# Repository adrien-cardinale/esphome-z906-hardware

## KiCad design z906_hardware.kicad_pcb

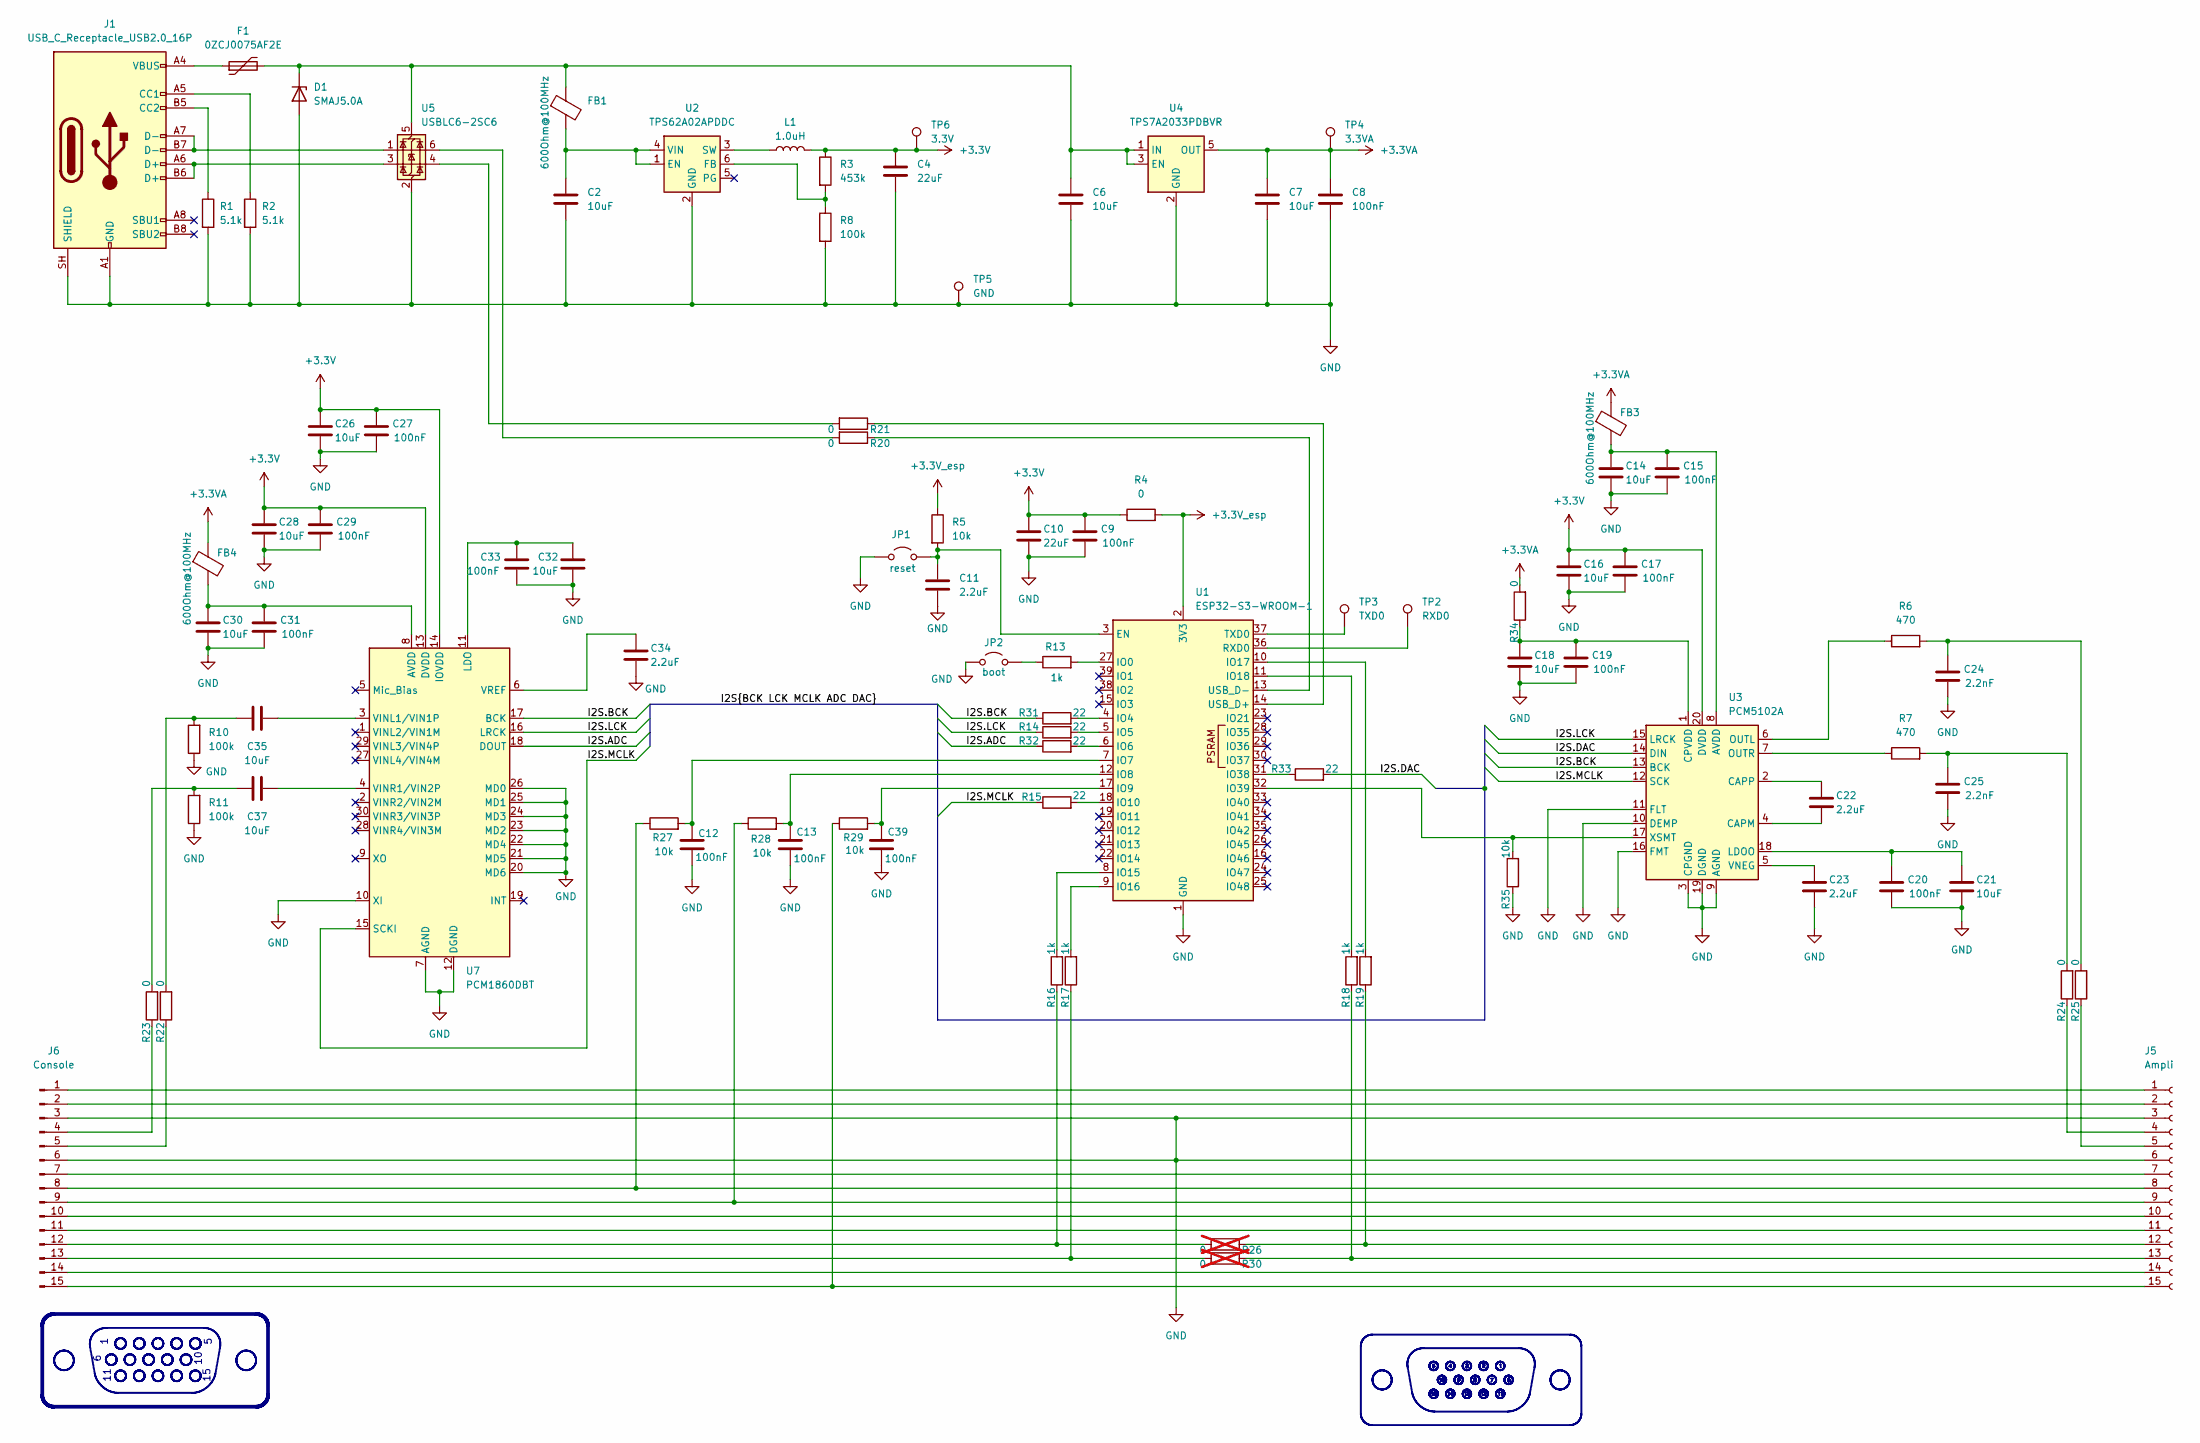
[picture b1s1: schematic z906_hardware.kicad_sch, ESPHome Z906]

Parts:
C2, C6, C7, C14, C16, C18, C21, C26, C28, C30, C32: 10uF; C_0805_2012Metric_Pad1.18x1.45mm_HandSolder
C4, C10: 22uF; C_0805_2012Metric_Pad1.18x1.45mm_HandSolder
C8, C9, C12, C13, C15, C17, C19, C20, C27, C29, C31, C33, C39: 100nF; C_0805_2012Metric_Pad1.18x1.45mm_HandSolder
C11, C22, C23, C34: 2.2uF; C_0805_2012Metric_Pad1.18x1.45mm_HandSolder
C24, C25: 2.2nF; C_0805_2012Metric_Pad1.18x1.45mm_HandSolder
C35, C37: 10uF; C_1206_3216Metric_Pad1.33x1.80mm_HandSolder
D1: SMAJ5.0A; D_SMA
F1: 0ZCJ0075AF2E; Fuse_1210_3225Metric
FB1, FB3, FB4: 600Ohm@100MHz; R_0805_2012Metric_Pad1.20x1.40mm_HandSolder
J1: USB_C_Receptacle_USB2.0_16P; USB_C_Receptacle_GCT_USB4105-xx-A_16P_TopMnt_Horizontal
J5: Ampli; TE_Micro-MaTch_1-215079-6_2x08_P1.27mm_Vertical
J6: Console; DSUB-15-HD_Pins_Horizontal_P2.29x1.90mm_EdgePinOffset3.03mm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
JP1: reset; TestPoint_2Pads_Pitch2.54mm_Drill0.8mm
JP2: boot; TestPoint_2Pads_Pitch2.54mm_Drill0.8mm
L1: 1.0uH; L_1008_2520Metric_Pad1.43x2.20mm_HandSolder
R1, R2: 5.1k; R_0805_2012Metric_Pad1.20x1.40mm_HandSolder
R3: 453k; R_0805_2012Metric_Pad1.20x1.40mm_HandSolder
R4, R20, R21, R22, R23, R24, R25, R34: 0; R_0805_2012Metric_Pad1.20x1.40mm_HandSolder
R5, R27, R28, R29, R35: 10k; R_0805_2012Metric_Pad1.20x1.40mm_HandSolder
R6, R7: 470; R_0805_2012Metric_Pad1.20x1.40mm_HandSolder
R8, R10, R11: 100k; R_0805_2012Metric_Pad1.20x1.40mm_HandSolder
R13, R16, R17, R18, R19: 1k; R_0805_2012Metric_Pad1.20x1.40mm_HandSolder
R14, R15, R31, R32, R33: 22; R_0805_2012Metric_Pad1.20x1.40mm_HandSolder
R26, R30: 0; R_0805_2012Metric_Pad1.20x1.40mm_HandSolder; not fitted
TP2: RXD0; Pin_D1.0mm_L10.0mm
TP3: TXD0; Pin_D1.0mm_L10.0mm
TP4: 3.3VA; Pin_D1.0mm_L10.0mm
TP5: GND; Pin_D1.0mm_L10.0mm
TP6: 3.3V; Pin_D1.0mm_L10.0mm
U1: ESP32-S3-WROOM-1
U2: TPS62A02APDDC; SOT-23-6
U3: PCM5102A; TSSOP-20_4.4x6.5mm_P0.65mm
U4: TPS7A2033PDBVR; SOT-23-5
U5: USBLC6-2SC6; SOT-23-6
U7: PCM1860DBT; TSSOP-30_4.4x7.8mm_P0.5mm

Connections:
+3.3V: C4.1, C9.1, C10.1, C16.1, C17.1, C26.1, C27.1, C28.1, C29.1, L1.2, R3.1, R4.1, TP6.1 (1_1), U3.20 (DVDD), U7.13 (DVDD), U7.14 (IOVDD)
+3.3VA: C7.1, C8.1, FB3.1, FB4.1, R34.2, TP4.1 (1_1), U4.5 (OUT)
+3.3V_esp: R4.2, R5.1, U1.2 (3V3)
/I2S.ADC: R32.1, U7.18 (DOUT)
/I2S.BCK: R31.1, U3.13 (BCK), U7.17 (BCK)
/I2S.DAC: R33.2, U3.14 (DIN)
/I2S.LCK: R14.1, U3.15 (LRCK), U7.16 (LRCK)
/I2S.MCLK: R15.1, U3.12 (SCK), U7.15 (SCKI)
GND: C2.2, C4.2, C6.2, C7.2, C8.2, C9.2, C10.2, C11.2, C12.2, C13.2, C14.2, C15.2, C16.2, C17.2, C18.2, C19.2, C20.2, C21.2, C23.2, C24.2, C25.2, C26.2, C27.2, C28.2, C29.2, C30.2, C31.2, C32.2, C33.2, C34.2, C39.2, D1.2 (A), J1.A1 (GND), J1.A12 (GND), J1.B1 (GND), J1.B12 (GND), J1.SH (SHIELD), J5.3, J5.6, J6.3, J6.6, JP1.1 (A), JP2.1 (A), R1.2, R2.2, R8.2, R10.1, R11.1, R35.1, TP5.1 (1_1), U1.1 (GND), U1.40 (GND), U1.41 (GND), U2.2 (GND), U3.3 (CPGND), U3.9 (AGND), U3.10 (DEMP), U3.11 (FLT), U3.16 (FMT), U3.19 (DGND), U4.2 (GND), U5.2 (GND), U7.7 (AGND), U7.10 (XI), U7.12 (DGND), U7.20 (MD6), U7.21 (MD5), U7.22 (MD4), U7.23 (MD2), U7.24 (MD3), U7.25 (MD1), U7.26 (MD0)
unnamed: C24.1, R6.2, R25.2
unnamed: C25.1, R7.2, R24.2
unnamed: C35.1, R10.2, R22.2
unnamed: C37.1, R11.2, R23.2
unnamed: C6.1, D1.1 (K), F1.2, FB1.1, U4.1 (IN), U4.3 (EN), U5.5 (VBUS)
unnamed: F1.1, J1.A4 (VBUS), J1.A9 (VBUS), J1.B4 (VBUS), J1.B9 (VBUS)
unnamed: J1.A5 (CC1), R2.1
unnamed: J1.B5 (CC2), R1.1
unnamed: J1.A6 (D+), J1.B6 (D+), U5.3 (I/O2)
unnamed: J1.A7 (D-), J1.B7 (D-), U5.1 (I/O1)
unnamed: J5.1, J6.1
unnamed: J5.2, J6.2
unnamed: J5.4, R24.1
unnamed: J5.5, R25.1
unnamed: J5.7, J6.7
unnamed: J5.8, J6.8, R27.1
unnamed: J5.9, J6.9, R28.1
unnamed: J5.10, J6.10
unnamed: J5.11, J6.11
unnamed: J5.12, R19.1, R26.1
unnamed: J5.13, R18.1, R30.1
unnamed: J5.14, J6.14
unnamed: J5.15, J6.15, R29.1
unnamed: J6.4, R23.1
unnamed: J6.5, R22.1
unnamed: J6.12, R16.1, R26.2
unnamed: J6.13, R17.1, R30.2
unnamed: C11.1, JP1.2 (B), R5.2, U1.3 (EN)
unnamed: JP2.2 (B), R13.1
unnamed: R20.2, U5.6 (I/O1)
unnamed: R21.2, U5.4 (I/O2)
unnamed: R13.2, U1.27 (IO0)
unnamed: R31.2, U1.4 (IO4)
unnamed: R14.2, U1.5 (IO5)
unnamed: R32.2, U1.6 (IO6)
unnamed: C12.1, R27.2, U1.7 (IO7)
unnamed: C13.1, R28.2, U1.12 (IO8)
unnamed: C39.1, R29.2, U1.17 (IO9)
unnamed: R15.2, U1.18 (IO10)
unnamed: R16.2, U1.8 (IO15)
unnamed: R17.2, U1.9 (IO16)
unnamed: R19.2, U1.10 (IO17)
unnamed: R18.2, U1.11 (IO18)
unnamed: R33.1, U1.31 (IO38)
unnamed: R35.2, U1.32 (IO39), U3.17 (XSMT)
unnamed: TP2.1 (1_1), U1.36 (RXD0)
unnamed: TP3.1 (1_1), U1.37 (TXD0)
unnamed: R21.1, U1.14 (USB_D+)
unnamed: R20.1, U1.13 (USB_D-)
unnamed: C2.1, FB1.2, U2.1 (EN), U2.4 (VIN)
unnamed: R3.2, R8.1, U2.6 (FB)
unnamed: L1.1, U2.3 (SW)
unnamed: C14.1, C15.1, FB3.2, U3.8 (AVDD)
unnamed: C22.2, U3.4 (CAPM)
unnamed: C22.1, U3.2 (CAPP)
unnamed: C18.1, C19.1, R34.1, U3.1 (CPVDD)
unnamed: C20.1, C21.1, U3.18 (LDOO)
unnamed: R6.1, U3.6 (OUTL)
unnamed: R7.1, U3.7 (OUTR)
unnamed: C23.1, U3.5 (VNEG)
unnamed: C30.1, C31.1, FB4.2, U7.8 (AVDD)
unnamed: C32.1, C33.1, U7.11 (LDO)
unnamed: C35.2, U7.3 (VINL1/VIN1P)
unnamed: C37.2, U7.4 (VINR1/VIN2P)
unnamed: C34.1, U7.6 (VREF)

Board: 2 copper layers, 89 parts (0 on the bottom side), 74 nets, no tracks yet.
